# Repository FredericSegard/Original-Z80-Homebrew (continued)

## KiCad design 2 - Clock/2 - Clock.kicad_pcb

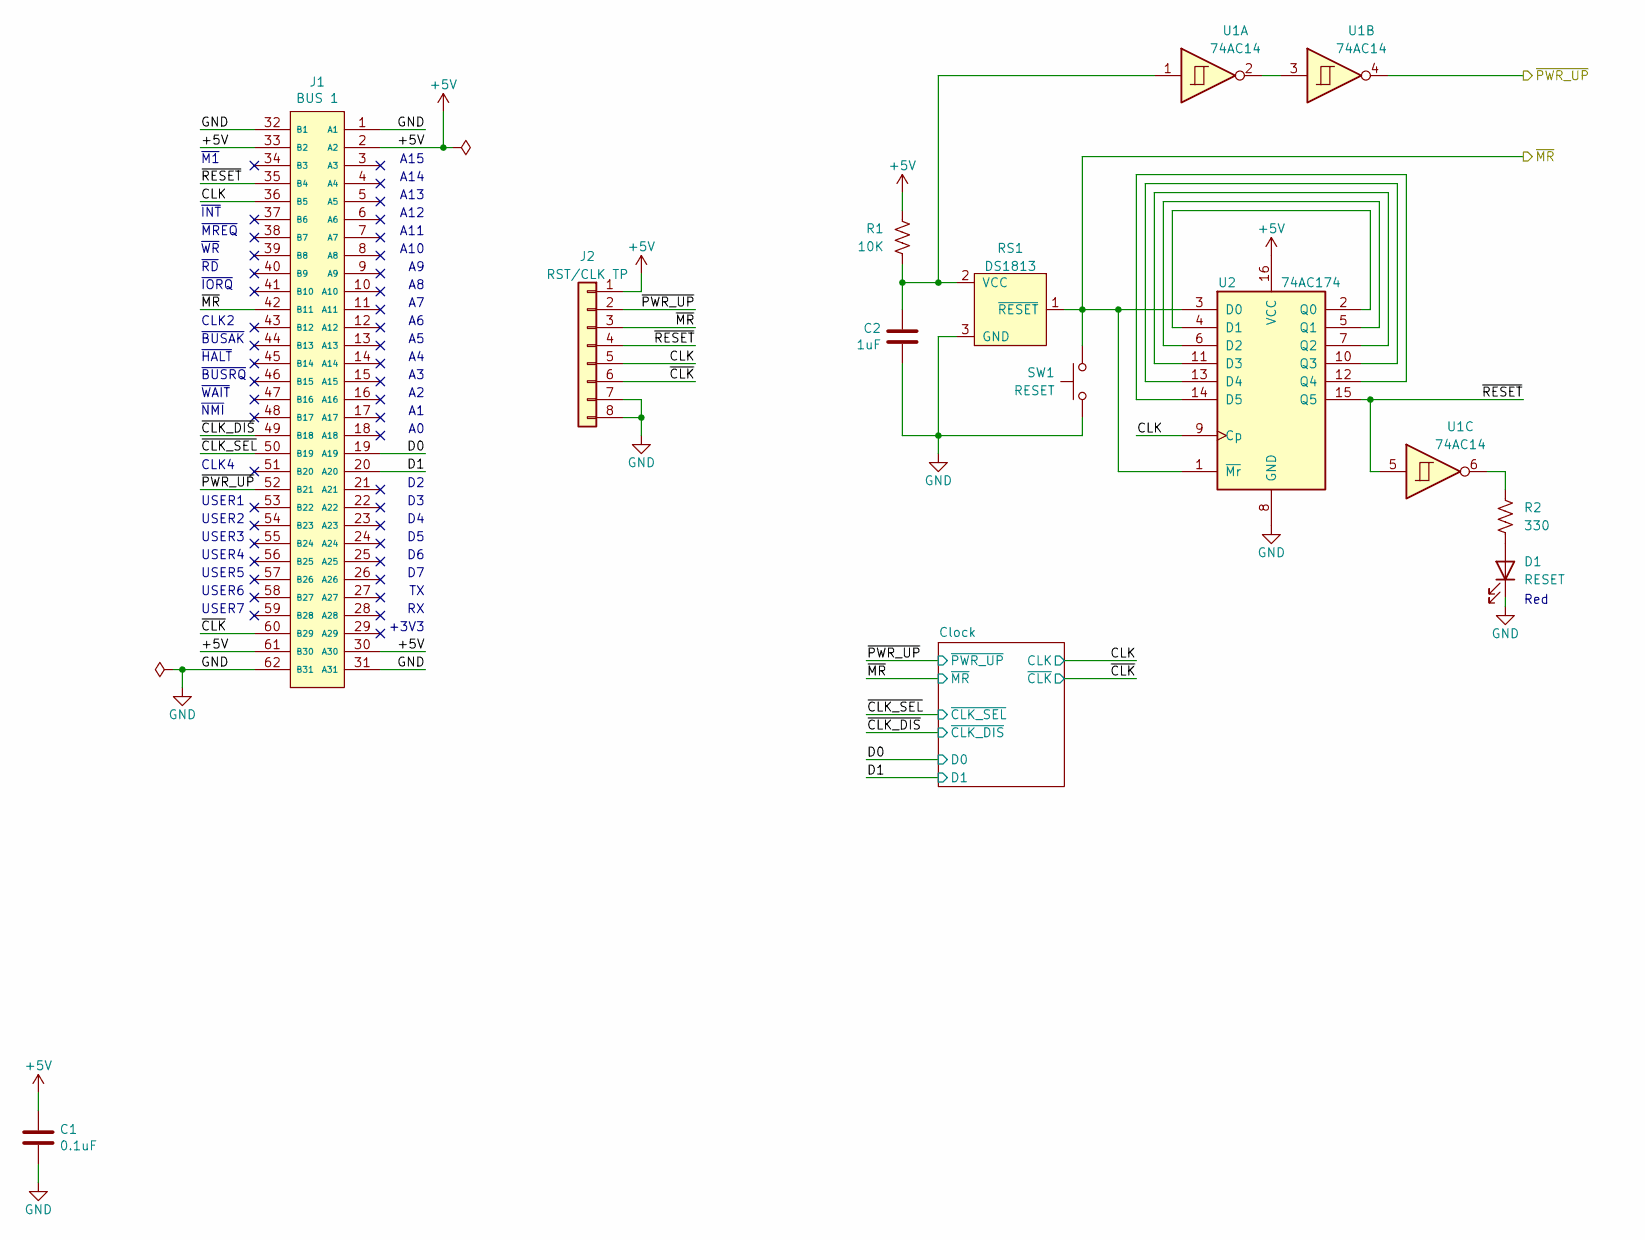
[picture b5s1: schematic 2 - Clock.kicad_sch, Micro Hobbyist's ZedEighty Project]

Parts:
C1: 0.1uF; C_Disc_D3.0mm_W2.0mm_P2.50mm
C2: 1uF; C_Disc_D3.0mm_W2.0mm_P2.50mm
D1: RESET; LED_D3.0mm_Horizontal_O1.27mm_Z2.0mm_Clear
J1: BUS 1; BUS_XT_Proto; Mouser Part Number 571-6-5530843-5
J2: RST/CLK TP; PinHeader_1x08_P2.54mm_Horizontal
R1: 10K; R_Axial_DIN0207_L6.3mm_D2.5mm_P10.16mm_Horizontal
R2: 330; R_Axial_DIN0207_L6.3mm_D2.5mm_P10.16mm_Horizontal
RS1: DS1813; TO-92L_Inline_Wide
SW1: RESET; SW_Tactile_SPST_Angled_PTS645Vx58-2LFS
U1: 74AC14; DIP-14_W7.62mm_Socket
U2: 74AC174; DIP-16_W7.62mm_Socket

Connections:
+5V: C1.1, J1.2 (A2), J1.30 (A30), J1.33 (B2), J1.61 (B30), J2.1, R1.2, U2.16 (VCC); also elsewhere on the board
/CLK: J1.36 (B5), J2.5, U2.9 (Cp); also elsewhere on the board
/D0: J1.19 (A19); also elsewhere on the board
/D1: J1.20 (A20); also elsewhere on the board
/~CLK_DIS: J1.49 (B18); also elsewhere on the board
/~CLK_SEL: J1.50 (B19); also elsewhere on the board
/~CLK: J1.60 (B29), J2.6; also elsewhere on the board
/~MR: J1.42 (B11), J2.3, RS1.1 (~RESET), SW1.1, U2.1 (~Mr), U2.3 (D0); also elsewhere on the board
/~PWR_UP: J1.52 (B21), J2.2, U1.4; also elsewhere on the board
/~RESET: J1.35 (B4), J2.4, U1.5, U2.15 (Q5)
GND: C1.2, C2.2, D1.1 (K), J1.1 (A1), J1.31 (A31), J1.32 (B1), J1.62 (B31), J2.7, J2.8, RS1.3 (GND), SW1.2, U2.8 (GND); also elsewhere on the board
unnamed: D1.2 (A), R2.2
unnamed: R2.1, U1.6
unnamed: C2.1, R1.1, RS1.2 (VCC), U1.1
unnamed: U1.2, U1.3
unnamed: U2.2 (Q0), U2.4 (D1)
unnamed: U2.5 (Q1), U2.6 (D2)
unnamed: U2.7 (Q2), U2.11 (D3)
unnamed: U2.10 (Q3), U2.13 (D4)
unnamed: U2.12 (Q4), U2.14 (D5)

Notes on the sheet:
A13
+3V3
USER6
~{NMI}
Red
~{RD}
A10
A11
USER2
USER5
A14
~{BUSRQ}
A15
~{IORQ}
USER3
CLK4
USER4
~{WR}
~{INT}
~{BUSAK}
CLK2
~{HALT}
USER7
~{MREQ}
~{WAIT}
USER1
A12
~{M1}

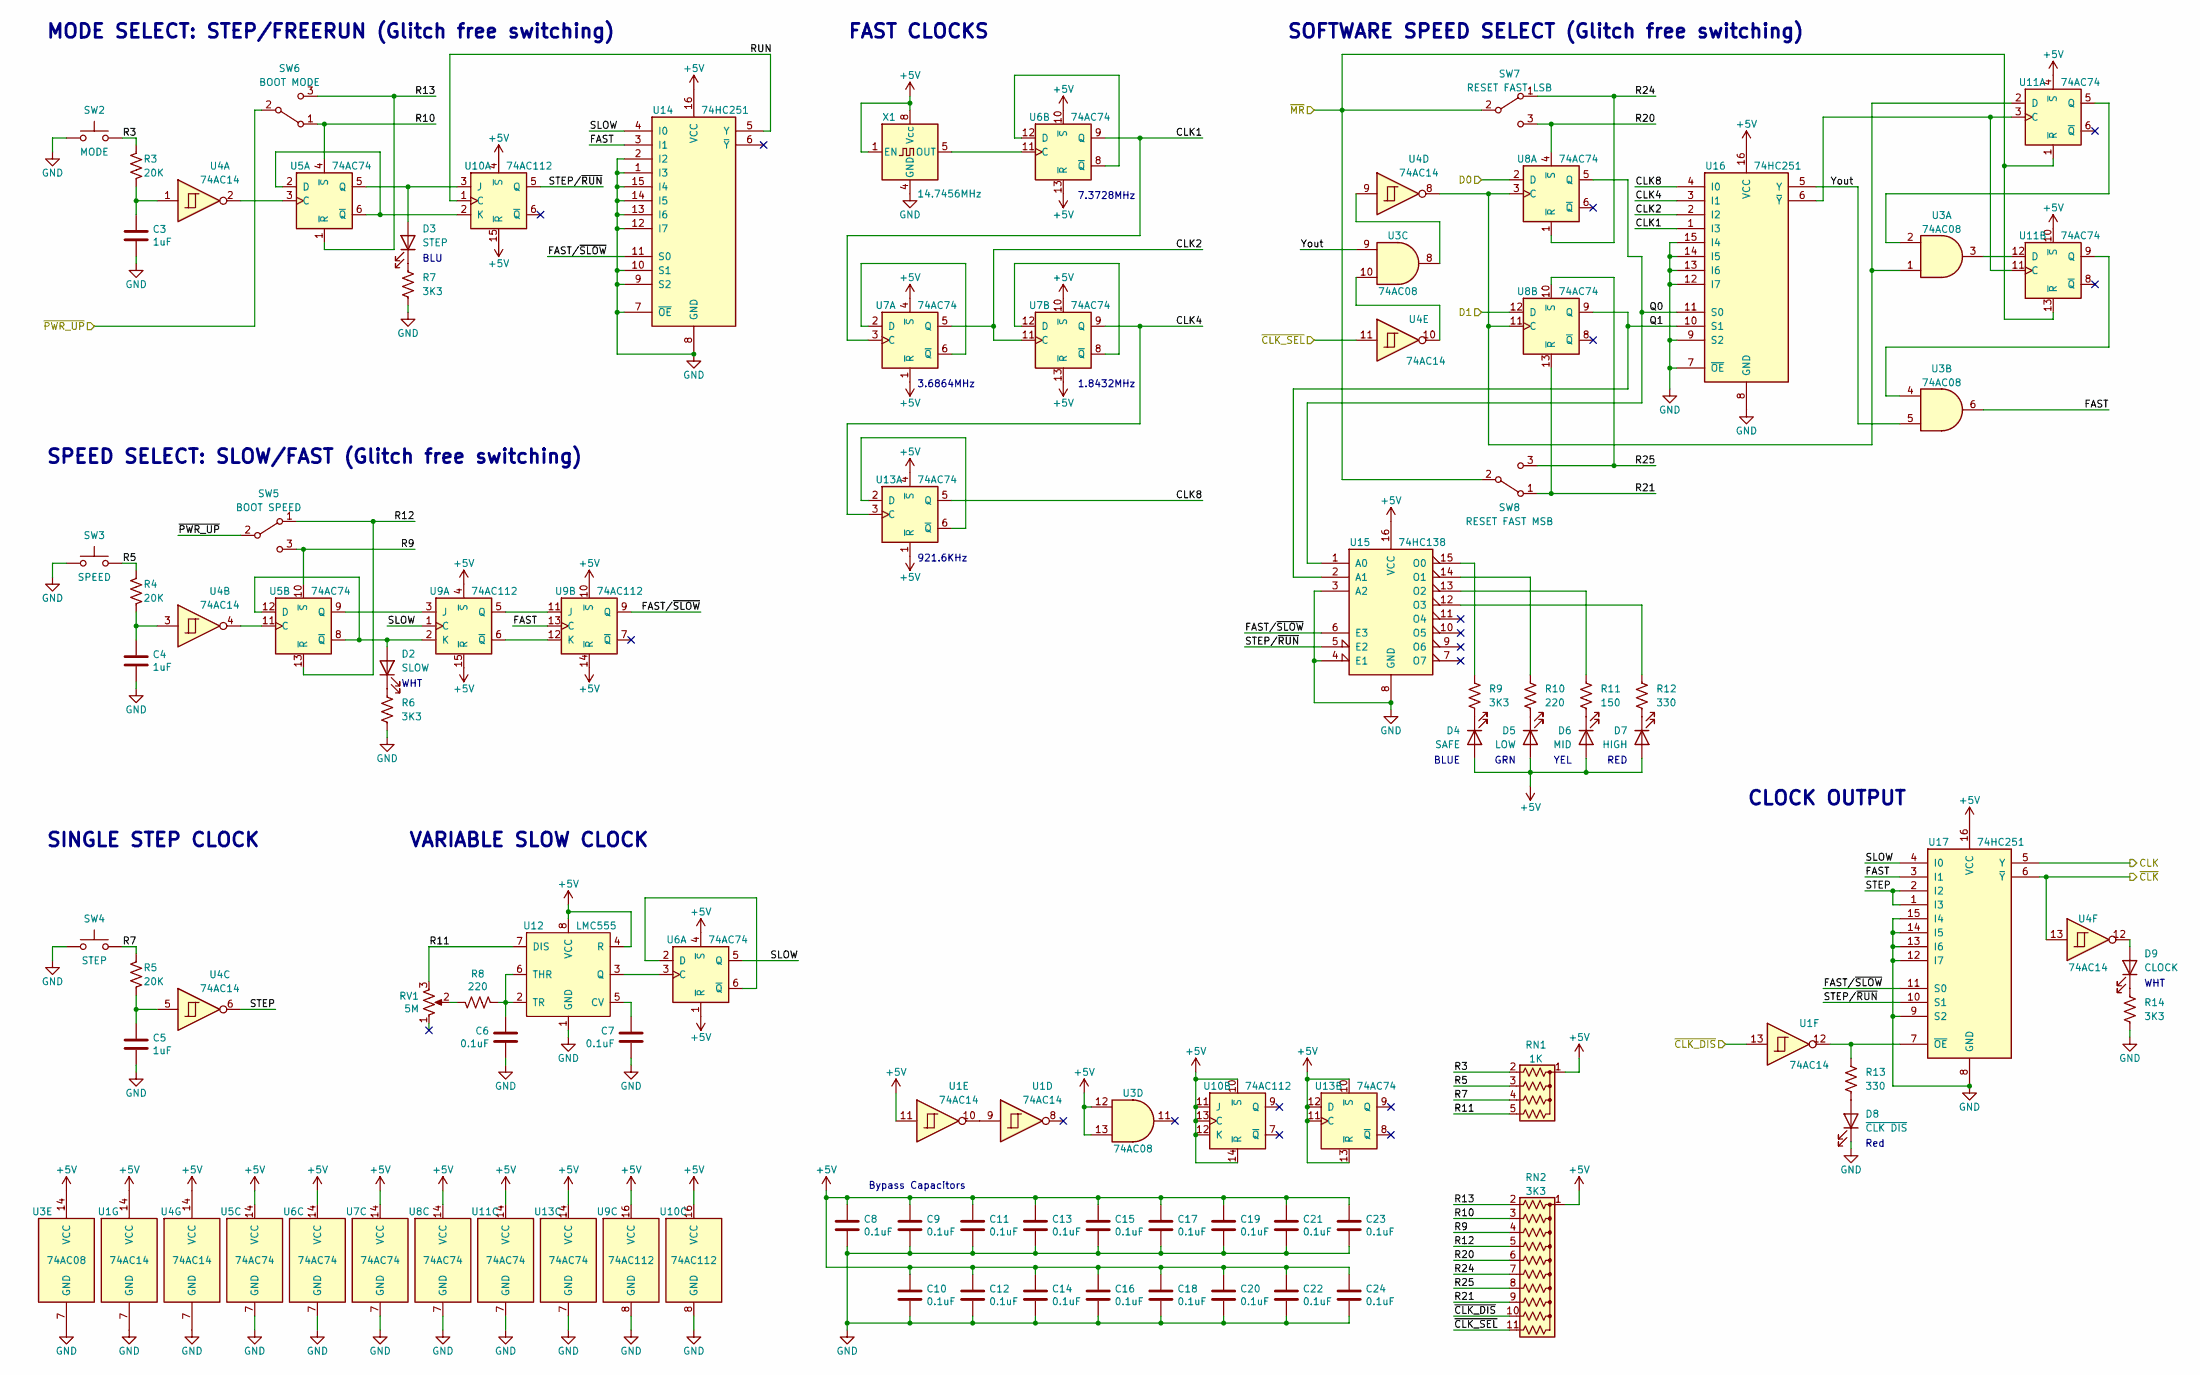
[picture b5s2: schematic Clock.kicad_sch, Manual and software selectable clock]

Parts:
C3, C4, C5: 1uF; C_Disc_D3.0mm_W1.6mm_P2.50mm
C6, C7, C8, C9, C10, C11, C12, C13, C14, C15, C16, C17, C18, C19, C20, C21, C22, C23, C24: 0.1uF; C_Disc_D3.0mm_W1.6mm_P2.50mm
D2: SLOW; LED_D3.0mm_Horizontal_O1.27mm_Z2.0mm_Clear
D3: STEP; LED_D3.0mm_Horizontal_O1.27mm_Z2.0mm_Clear
D4: SAFE; LED_D3.0mm_Horizontal_O1.27mm_Z2.0mm_Clear
D5: LOW; LED_D3.0mm_Horizontal_O1.27mm_Z2.0mm_Clear
D6: MID; LED_D3.0mm_Horizontal_O1.27mm_Z2.0mm_Clear
D7: HIGH; LED_D3.0mm_Horizontal_O1.27mm_Z2.0mm_Clear
D8: ~{CLK DIS}; LED_D3.0mm_Horizontal_O1.27mm_Z2.0mm_Clear
D9: CLOCK; LED_D3.0mm_Horizontal_O1.27mm_Z2.0mm_Clear
R3, R4, R5: 20K; R_Axial_DIN0207_L6.3mm_D2.5mm_P10.16mm_Horizontal
R6, R7, R9, R14: 3K3; R_Axial_DIN0207_L6.3mm_D2.5mm_P10.16mm_Horizontal
R8, R10: 220; R_Axial_DIN0207_L6.3mm_D2.5mm_P10.16mm_Horizontal
R11: 150; R_Axial_DIN0207_L6.3mm_D2.5mm_P10.16mm_Horizontal
R12, R13: 330; R_Axial_DIN0207_L6.3mm_D2.5mm_P10.16mm_Horizontal
RN1: 1K; R_Array_SIP5
RN2: 3K3; R_Array_SIP11
RV1: 5M; Potentiometer_Bourns_3296Z_Horizontal
SW2: MODE; SW_Tactile_SPST_Angled_PTS645Vx58-2LFS
SW3: SPEED; SW_Tactile_SPST_Angled_PTS645Vx58-2LFS
SW4: STEP; SW_Tactile_SPST_Angled_PTS645Vx58-2LFS
SW5: BOOT SPEED; Microswitch_4.7mm_spacing
SW6: BOOT MODE; Microswitch_4.7mm_spacing
SW7: RESET FAST LSB; Microswitch_4.7mm_spacing
SW8: RESET FAST MSB; Microswitch_4.7mm_spacing
U1, U4: 74AC14; DIP-14_W7.62mm_Socket
U3: 74AC08; DIP-14_W7.62mm_Socket
U5, U6, U7, U8, U11, U13: 74AC74; DIP-14_W7.62mm_Socket
U9, U10: 74AC112; DIP-16_W7.62mm_Socket
U12: LMC555; DIP-8_W7.62mm_Socket
U14, U16, U17: 74HC251; DIP-16_W7.62mm_Socket
U15: 74HC138; DIP-16_W7.62mm_Socket
X1: 14.7456MHz; DIP-8-4_W7.62mm_Oscillator_Socket

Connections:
+5V: C8.1, C9.1, C10.1, C11.1, C12.1, C13.1, C14.1, C15.1, C16.1, C17.1, C18.1, C19.1, C20.1, C21.1, C22.1, C23.1, C24.1, D4.2 (A), D5.2 (A), D6.2 (A), D7.2 (A), RN1.1 (common), RN2.1 (common), U1.11, U1.14 (VCC), U3.12, U3.13, U3.14 (VCC), U4.14 (VCC), U5.14 (VCC), U6.1 (~R), U6.4 (~S), U6.10 (~S), U6.13 (~R), U6.14 (VCC), U7.1 (~R), U7.4 (~S), U7.10 (~S), U7.13 (~R), U7.14 (VCC), U8.14 (VCC), U9.4 (~S), U9.10 (~S), U9.14 (~R), U9.15 (~R), U9.16 (VCC), U10.4 (~S), U10.10 (~S), U10.11 (J), U10.12 (K), U10.13 (C), U10.14 (~R), U10.15 (~R), U10.16 (VCC), U11.4 (~S), U11.10 (~S), U11.14 (VCC), U12.4 (R), U12.8 (VCC), U13.1 (~R), U13.4 (~S), U13.10 (~S), U13.11 (C), U13.12 (D), U13.13 (~R), U13.14 (VCC), U14.16 (VCC), U15.16 (VCC), U16.16 (VCC), U17.16 (VCC), X1.1 (EN), X1.8 (Vcc); also elsewhere on the board
/CLK: U17.5 (Y); also elsewhere on the board
/Clock/CLK1: U6.9 (Q), U7.3 (C), U16.1 (I3)
/Clock/CLK2: U7.5 (Q), U7.11 (C), U16.2 (I2)
/Clock/CLK4: U7.9 (Q), U13.3 (C), U16.3 (I1)
/Clock/CLK8: U13.5 (Q), U16.4 (I0)
/Clock/FAST: U3.6, U9.13 (C), U14.3 (I1), U17.3 (I1)
/Clock/FAST/~SLOW: U9.9 (Q), U14.11 (S0), U15.6 (E3), U17.11 (S0)
/Clock/Q0: U8.5 (Q), U15.1 (A0), U16.11 (S0)
/Clock/Q1: U8.9 (Q), U15.2 (A1), U16.10 (S1)
/Clock/R3: R3.2, RN1.2 (R1), SW2.1
/Clock/R5: R4.2, RN1.3 (R2), SW3.1
/Clock/R7: R5.2, RN1.4 (R3), SW4.1
/Clock/R9: RN2.4 (R3), SW5.3 (C), U5.10 (~S)
/Clock/R10: RN2.3 (R2), SW6.1 (A), U5.4 (~S)
/Clock/R11: RN1.5 (R4), RV1.3, U12.7 (DIS)
/Clock/R12: RN2.5 (R4), SW5.1 (A), U5.13 (~R)
/Clock/R13: RN2.2 (R1), SW6.3 (C), U5.1 (~R)
/Clock/R20: RN2.6 (R5), SW7.3 (C), U8.4 (~S)
/Clock/R21: RN2.9 (R8), SW8.1 (A), U8.13 (~R)
/Clock/R24: RN2.7 (R6), SW7.1 (A), U8.1 (~R)
/Clock/R25: RN2.8 (R7), SW8.3 (C), U8.10 (~S)
/Clock/RUN: U10.1 (C), U14.5 (Y)
/Clock/SLOW: U6.5 (Q), U9.1 (C), U14.4 (I0), U17.4 (I0)
/Clock/STEP: U4.6, U17.1 (I3), U17.2 (I2)
/Clock/STEP/~RUN: U10.5 (Q), U15.5 (E2), U17.10 (S1)
/Clock/Yout: U3.5, U3.9, U16.5 (Y)
/D0: U8.2 (D); also elsewhere on the board
/D1: U8.12 (D); also elsewhere on the board
/~CLK_DIS: RN2.10 (R9), U1.13; also elsewhere on the board
/~CLK_SEL: RN2.11 (R10), U4.11; also elsewhere on the board
/~CLK: U4.13, U17.6 (~Y); also elsewhere on the board
/~MR: SW7.2 (B), SW8.2 (B), U11.1 (~R), U11.13 (~R); also elsewhere on the board
/~PWR_UP: SW5.2 (B), SW6.2 (B); also elsewhere on the board
GND: C3.2, C4.2, C5.2, C6.2, C7.2, C8.2, C9.2, C10.2, C11.2, C12.2, C13.2, C14.2, C15.2, C16.2, C17.2, C18.2, C19.2, C20.2, C21.2, C22.2, C23.2, C24.2, D8.1 (K), R6.2, R7.2, R14.2, SW2.2, SW3.2, SW4.2, U1.7 (GND), U3.7 (GND), U4.7 (GND), U5.7 (GND), U6.7 (GND), U7.7 (GND), U8.7 (GND), U9.8 (GND), U10.8 (GND), U11.7 (GND), U12.1 (GND), U13.7 (GND), U14.1 (I3), U14.2 (I2), U14.7 (~OE), U14.8 (GND), U14.9 (S2), U14.10 (S1), U14.12 (I7), U14.13 (I6), U14.14 (I5), U14.15 (I4), U15.3 (A2), U15.4 (E1), U15.8 (GND), U16.7 (~OE), U16.8 (GND), U16.9 (S2), U16.12 (I7), U16.13 (I6), U16.14 (I5), U16.15 (I4), U17.8 (GND), U17.9 (S2), U17.12 (I7), U17.13 (I6), U17.14 (I5), U17.15 (I4), X1.4 (GND); also elsewhere on the board
unnamed: C3.1, R3.1, U4.1
unnamed: C4.1, R4.1, U4.3
unnamed: C5.1, R5.1, U4.5
unnamed: D2.2 (A), U5.8 (~Q), U5.12 (D), U9.2 (K)
unnamed: D2.1 (K), R6.1
unnamed: D3.2 (A), U5.5 (Q), U10.3 (J)
unnamed: D3.1 (K), R7.1
unnamed: D4.1 (K), R9.2
unnamed: D5.1 (K), R10.2
unnamed: D6.1 (K), R11.2
unnamed: D7.1 (K), R12.2
unnamed: D8.2 (A), R13.2
unnamed: D9.2 (A), U4.12
unnamed: D9.1 (K), R14.1
unnamed: R8.1, RV1.2
unnamed: U1.9, U1.10
unnamed: U3.8, U4.9
unnamed: U3.10, U4.10
unnamed: U4.2, U5.3 (C)
unnamed: U4.4, U5.11 (C)
unnamed: U5.9 (Q), U9.3 (J)
unnamed: U6.2 (D), U6.6 (~Q)
unnamed: U6.11 (C), X1.5 (OUT)
unnamed: U6.8 (~Q), U6.12 (D)
unnamed: U7.2 (D), U7.6 (~Q)
unnamed: U7.8 (~Q), U7.12 (D)
unnamed: U9.5 (Q), U9.11 (J)
unnamed: U9.6 (~Q), U9.12 (K)
unnamed: U5.2 (D), U5.6 (~Q), U10.2 (K)
unnamed: U11.3 (C), U11.11 (C), U16.6 (~Y)
unnamed: U3.1, U4.8, U8.3 (C), U8.11 (C), U11.2 (D)
unnamed: U3.2, U11.5 (Q)
unnamed: U3.3, U11.12 (D)
unnamed: U3.4, U11.9 (Q)
unnamed: C7.1, U12.5 (CV)
unnamed: U6.3 (C), U12.3 (Q)
unnamed: C6.1, R8.2, U12.2 (TR), U12.6 (THR)
unnamed: U13.2 (D), U13.6 (~Q)
unnamed: R9.1, U15.15 (O0)
unnamed: R10.1, U15.14 (O1)
unnamed: R11.1, U15.13 (O2)
unnamed: R12.1, U15.12 (O3)
unnamed: R13.1, U1.12, U17.7 (~OE)

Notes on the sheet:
3.6864MHz
VARIABLE SLOW CLOCK
SPEED SELECT: SLOW/FAST (Glitch free switching)
Bypass Capacitors
MODE SELECT: STEP/FREERUN (Glitch free switching)
RED
FAST CLOCKS
SOFTWARE SPEED SELECT (Glitch free switching)
CLOCK OUTPUT
921.6KHz
GRN
WHT
1.8432MHz
BLU
Red
7.3728MHz
YEL
BLUE
SINGLE STEP CLOCK

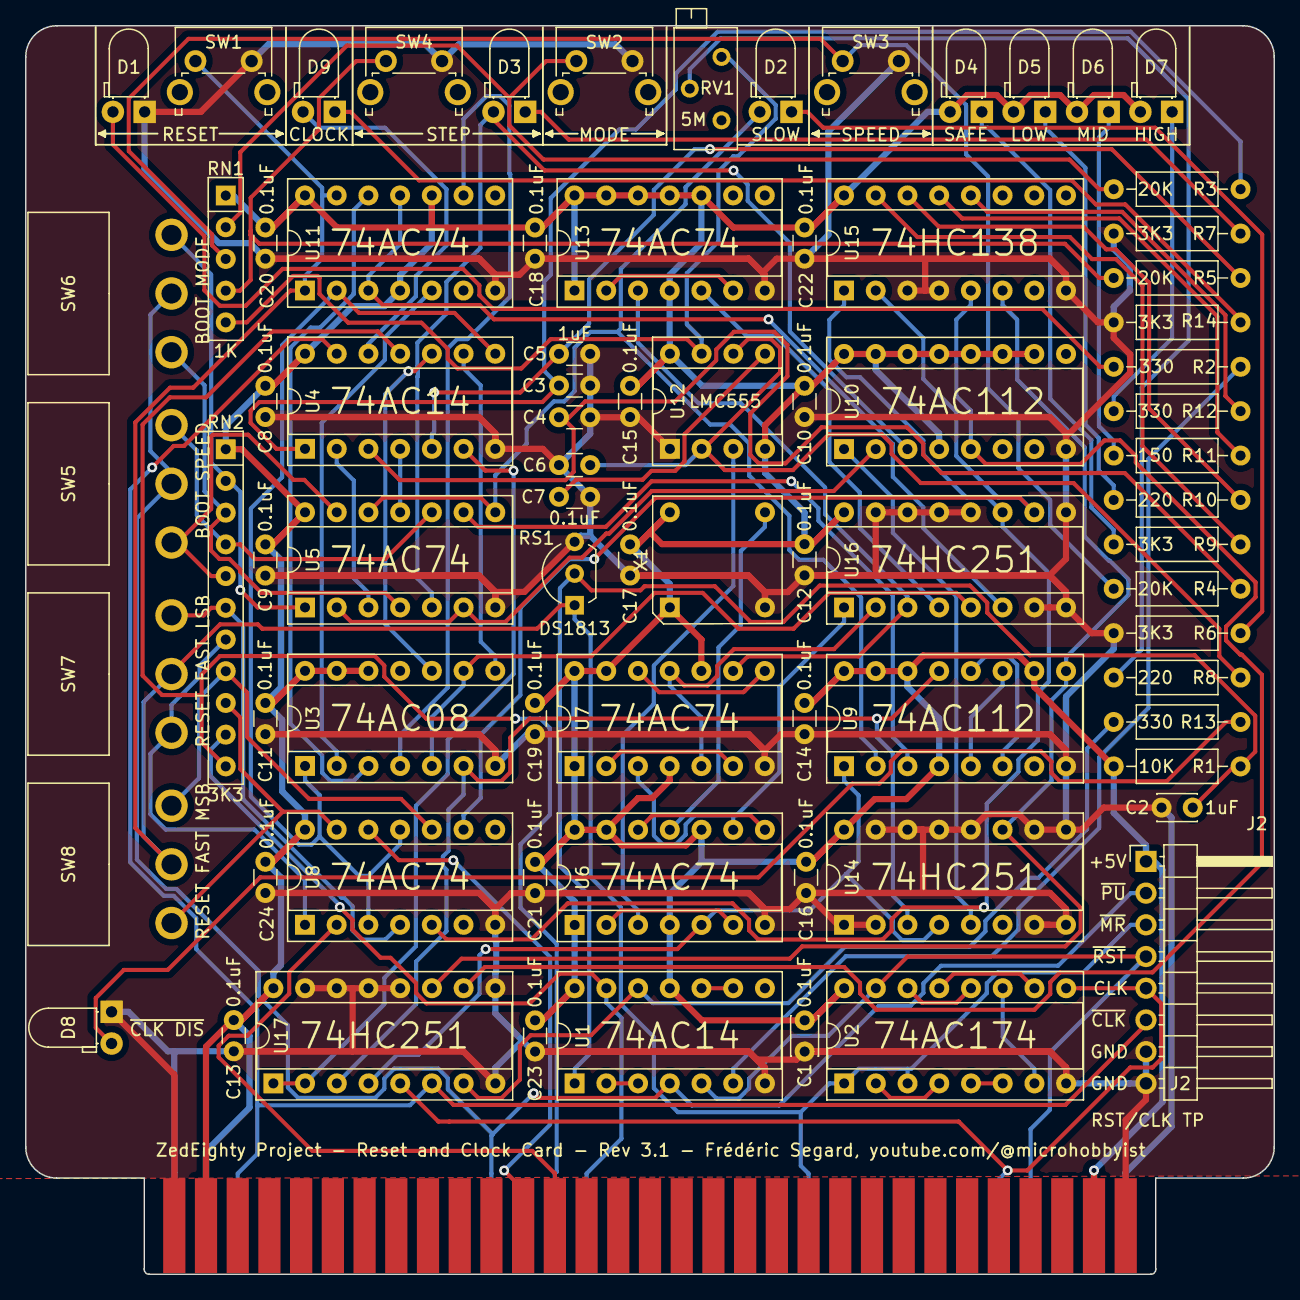
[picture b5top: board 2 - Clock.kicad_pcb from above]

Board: 2 copper layers, 100.0 x 100.0 mm, 79 parts (0 on the bottom side), 88 nets.

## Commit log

2023-08-22 Converted files from version 6 to 7 of KiCad
2023-08-22 Clock card updated
2023-08-22 Imported CPU card without converting Kicad 6 to 7 problems
2023-08-22 Finished cleaning up the project
2023-08-22 Added gerbers
2023-08-24 Added serial card, still needs work
2023-08-25 In the process of routing the board
2023-08-26 Made a mess of things a bit.
    Software clock is non-functional. Worked on the breadboard, but makes the CPU board crash when writing to the IO port to select clock speed.
2023-09-11 Rerouted some traces and readied the the gerber to send out to manufacturing
2023-09-11 Generic updated
2023-12-28 Misc changes
